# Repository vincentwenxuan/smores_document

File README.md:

# smores_document
smores document for adding comments and documentation to smores program

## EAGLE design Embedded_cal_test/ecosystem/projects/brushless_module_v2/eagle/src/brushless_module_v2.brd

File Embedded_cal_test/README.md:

Embedded
========
Embedded Software for SMORES, including STM32F303 part, ATmega88 part and Gumstix part.

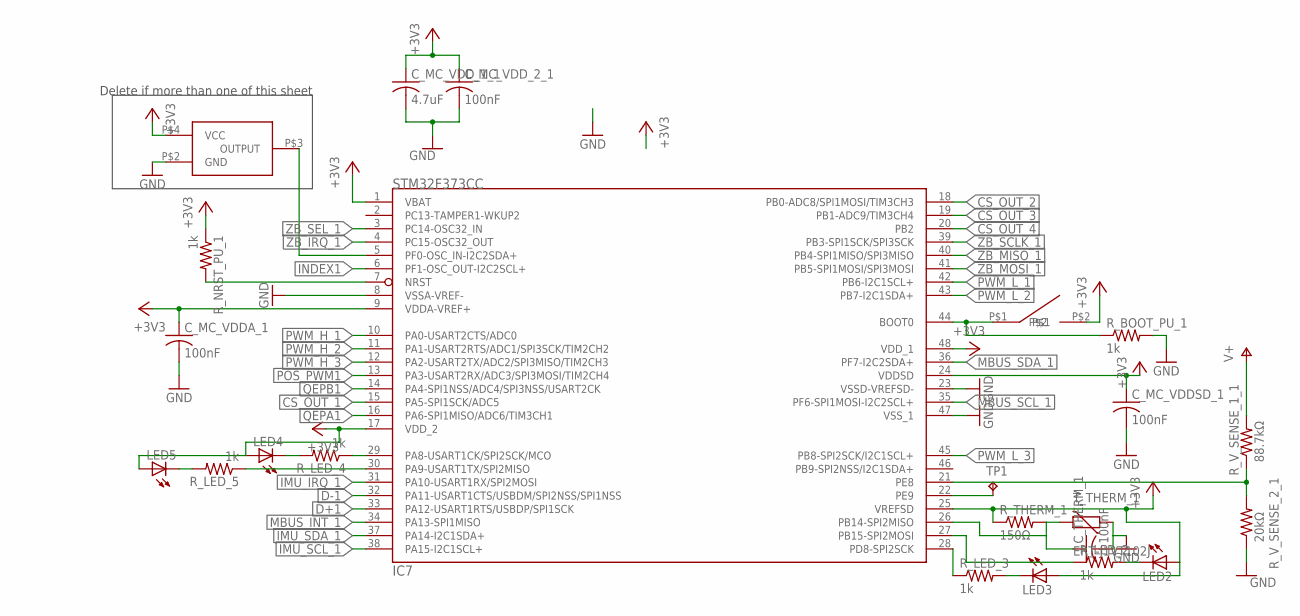
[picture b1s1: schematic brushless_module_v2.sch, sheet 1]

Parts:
C_MC_VDDA_1: 100nF; C0603
C_MC_VDDSD_1: 100nF; C0603
C_MC_VDD_1_1: 4.7uF; C0603
C_MC_VDD_2_1: 100nF; C0603
C_THERM_1: 100nF; C0603
IC7: STM32F373CC; LQFP48
LED2, LED3, LED4, LED5: LEDCHIPLED_0603; CHIPLED_0603
OSC1: FOX924B; 4-SMD_5X3.2
R_BOOT_PU_1: 1k; R0603
R_LED_2, R_LED_3, R_LED_4, R_LED_5: 1k; R0603
R_NRST_PU_1: 1k; R0603
R_THERM_1: 150Ω; R0603
R_V_SENSE_1_1: 88.7kΩ; R0603
R_V_SENSE_2_1: 20kΩ; R0603
SW1: B3U
TP1: TPTP10R; TP10R
T_THERM_1: ERT-J1VT102J; CT/CN0603

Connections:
16MHZ_3V3: IC7.5 (PF0-OSC_IN-I2C2SDA+), OSC1.P$3 (OUTPUT); also elsewhere on the board
+3V3: C_MC_VDDA_1.1, C_MC_VDDSD_1.1, C_MC_VDD_1_1.1, C_MC_VDD_2_1.1, IC7.1 (VBAT), IC7.9 (VDDA-VREF+), IC7.17 (VDD_2), IC7.24 (VDDSD), IC7.25 (VREFSD), IC7.48 (VDD_1), LED2.A, LED3.A, LED4.A, LED5.A, OSC1.P$4 (VCC), R_NRST_PU_1.1, R_THERM_1.1, SW1.P$2; also elsewhere on the board
BOOT0_1: IC7.44 (BOOT0), R_BOOT_PU_1.1, SW1.P$1
CS_OUT_1: IC7.15 (PA5-SPI1SCK/ADC5); also elsewhere on the board
CS_OUT_2: IC7.18 (PB0-ADC8/SPI1MOSI/TIM3CH3); also elsewhere on the board
CS_OUT_3: IC7.19 (PB1-ADC9/TIM3CH4); also elsewhere on the board
CS_OUT_4: IC7.20 (PB2); also elsewhere on the board
D+1: IC7.33 (PA12-USART1RTS/USBDP/SPI1SCK); also elsewhere on the board
D-1: IC7.32 (PA11-USART1CTS/USBDM/SPI2NSS/SPI1NSS); also elsewhere on the board
GND: C_MC_VDDA_1.2, C_MC_VDDSD_1.2, C_MC_VDD_1_1.2, C_MC_VDD_2_1.2, C_THERM_1.2, IC7.8 (VSSA-VREF-), IC7.23 (VSSD-VREFSD-), IC7.47 (VSS_1), OSC1.P$2 (GND), R_BOOT_PU_1.2, R_V_SENSE_2_1.1, T_THERM_1.1; also elsewhere on the board
IMU_IRQ_1: IC7.31 (PA10-USART1RX/SPI2MOSI); also elsewhere on the board
IMU_SCL_1: IC7.38 (PA15-I2C1SCL+); also elsewhere on the board
IMU_SDA_1: IC7.37 (PA14-I2C1SDA+); also elsewhere on the board
INDEX1: IC7.6 (PF1-OSC_OUT-I2C2SCL+); also elsewhere on the board
MBUS_INT_1: IC7.34 (PA13-SPI1MISO); also elsewhere on the board
MBUS_SCL_1: IC7.35 (PF6-SPI1MOSI-I2C2SCL+); also elsewhere on the board
MBUS_SDA_1: IC7.36 (PF7-I2C2SDA+); also elsewhere on the board
unnamed: IC7.21 (PE8), R_V_SENSE_1_1.1, R_V_SENSE_2_1.2
unnamed: LED2.C, R_LED_2.2
unnamed: LED3.C, R_LED_3.2
unnamed: IC7.27 (PB15-SPI2MOSI), R_LED_2.1
unnamed: IC7.28 (PD8-SPI2SCK), R_LED_3.1
unnamed: LED4.C, R_LED_4.2
unnamed: LED5.C, R_LED_5.2
unnamed: IC7.29 (PA8-USART1CK/SPI2SCK/MCO), R_LED_4.1
unnamed: IC7.30 (PA9-USART1TX/SPI2MISO), R_LED_5.1
unnamed: IC7.22 (PE9), TP1.TP
NRST_1: IC7.7 (NRST), R_NRST_PU_1.2
POS_PWM1: IC7.13 (PA3-USART2RX/ADC3/SPI3MOSI/TIM2CH4); also elsewhere on the board
PWM_H_1: IC7.10 (PA0-USART2CTS/ADC0); also elsewhere on the board
PWM_H_2: IC7.11 (PA1-USART2RTS/ADC1/SPI3SCK/TIM2CH2); also elsewhere on the board
PWM_H_3: IC7.12 (PA2-USART2TX/ADC2/SPI3MISO/TIM2CH3); also elsewhere on the board
PWM_L_1: IC7.42 (PB6-I2C1SCL+); also elsewhere on the board
PWM_L_2: IC7.43 (PB7-I2C1SDA+); also elsewhere on the board
PWM_L_3: IC7.45 (PB8-SPI2SCK/I2C1SCL+); also elsewhere on the board
QEPA1: IC7.16 (PA6-SPI1MISO/ADC6/TIM3CH1); also elsewhere on the board
QEPB1: IC7.14 (PA4-SPI1NSS/ADC4/SPI3NSS/USART2CK); also elsewhere on the board
THERM: C_THERM_1.1, IC7.26 (PB14-SPI2MISO), R_THERM_1.2, T_THERM_1.2
V+: R_V_SENSE_1_1.2; also elsewhere on the board
ZB_IRQ_1: IC7.4 (PC15-OSC32_OUT); also elsewhere on the board
ZB_MISO_1: IC7.40 (PB4-SPI1MISO/SPI3MISO); also elsewhere on the board
ZB_MOSI_1: IC7.41 (PB5-SPI1MOSI/SPI3MOSI); also elsewhere on the board
ZB_SCLK_1: IC7.39 (PB3-SPI1SCK/SPI3SCK); also elsewhere on the board
ZB_SEL_1: IC7.3 (PC14-OSC32_IN); also elsewhere on the board

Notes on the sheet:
Delete if more than one of this sheet

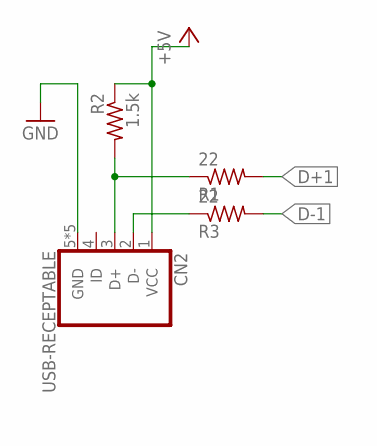
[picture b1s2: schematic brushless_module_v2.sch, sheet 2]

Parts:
CN2: USB-RECEPTABLE; FCI-10103594-0001LF
R1, R3: 22; R0603
R2: 1.5k; R0603

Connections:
+5V: CN2.1 (VCC), R2.1; also elsewhere on the board
D+1: R1.2; also elsewhere on the board
D+_IN_1: CN2.3 (D+), R1.1, R2.2
D-1: R3.2; also elsewhere on the board
D-_IN_1: CN2.2 (D-), R3.1
GND: CN2.5 (GND), CN2.P$1 (GND), CN2.P$2 (GND), CN2.P$3 (GND), CN2.P$4 (GND); also elsewhere on the board

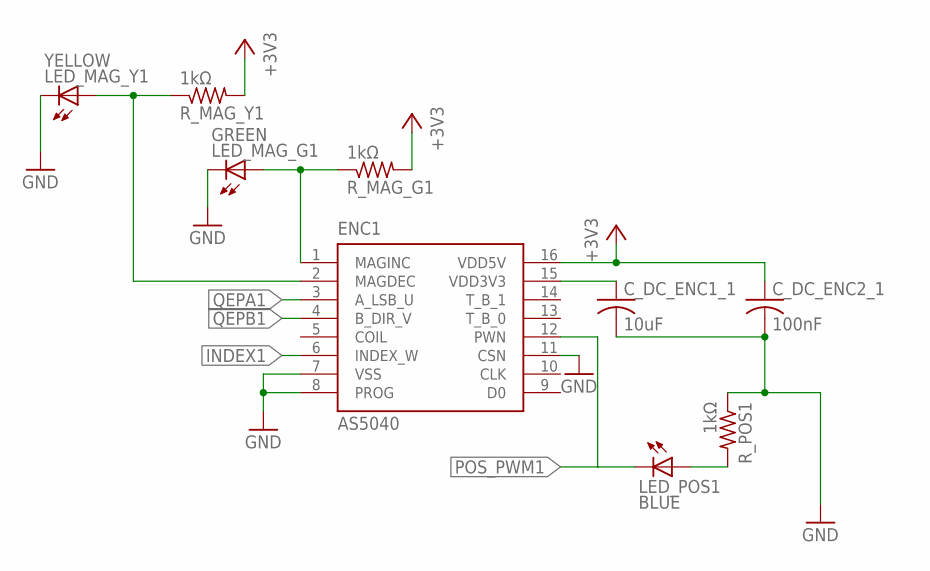
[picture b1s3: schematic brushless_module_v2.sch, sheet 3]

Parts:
C_DC_ENC1_1: 10uF; C0603
C_DC_ENC2_1: 100nF; C0603
ENC1: AS5040; SSOP16
LED_MAG_G1: GREEN; CHIP-LED0603
LED_MAG_Y1: YELLOW; CHIP-LED0603
LED_POS1: BLUE; CHIP-LED0603
R_MAG_G1: 1kΩ; R0603
R_MAG_Y1: 1kΩ; R0603
R_POS1: 1kΩ; R0603

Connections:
+3V3: C_DC_ENC2_1.1, ENC1.16 (VDD5V), R_MAG_G1.2, R_MAG_Y1.2; also elsewhere on the board
ENC_3V3_1: C_DC_ENC1_1.1, ENC1.15 (VDD3V3)
GND: C_DC_ENC1_1.2, C_DC_ENC2_1.2, ENC1.7 (VSS), ENC1.8 (PROG), ENC1.11 (CSN), LED_MAG_G1.C, LED_MAG_Y1.C, R_POS1.1; also elsewhere on the board
INDEX1: ENC1.6 (INDEX_W); also elsewhere on the board
MAGDEC1: ENC1.2 (MAGDEC), LED_MAG_Y1.A, R_MAG_Y1.1
MAGINC1: ENC1.1 (MAGINC), LED_MAG_G1.A, R_MAG_G1.1
unnamed: LED_POS1.A, R_POS1.2
POS_PWM1: ENC1.12 (PWN), LED_POS1.C; also elsewhere on the board
QEPA1: ENC1.3 (A_LSB_U); also elsewhere on the board
QEPB1: ENC1.4 (B_DIR_V); also elsewhere on the board

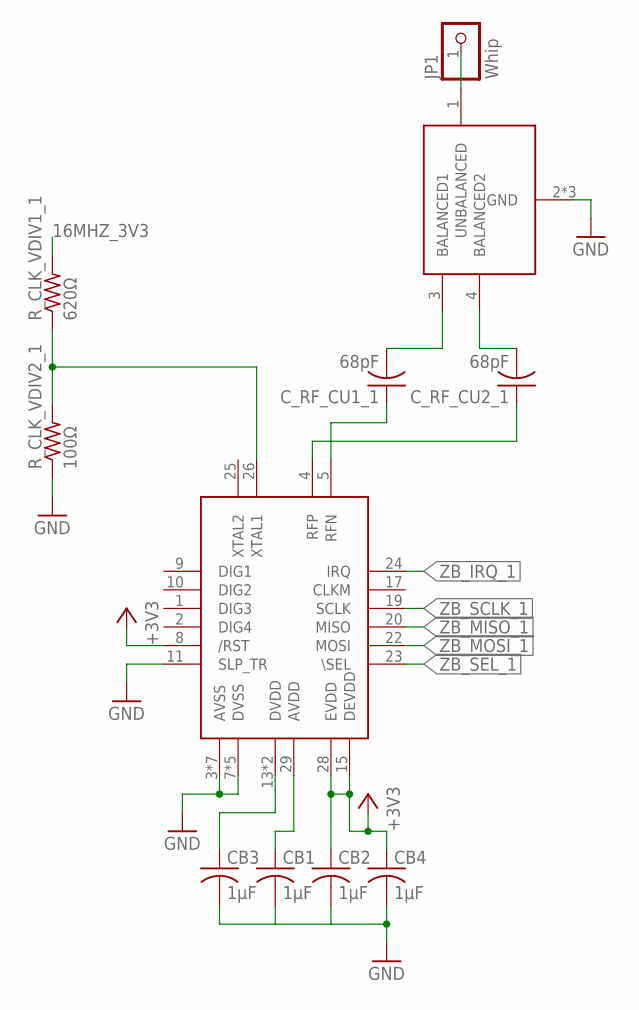
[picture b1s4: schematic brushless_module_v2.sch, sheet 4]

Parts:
BALUN1: 0896FB15A0100
CB1, CB2, CB3, CB4: 1µF; C0603
C_RF_CU1_1, C_RF_CU2_1: 68pF; C0603
JP1: Whip; 1X01M
RADIO1: AT86RF; QFNN32
R_CLK_VDIV1_1: 620Ω; R0603
R_CLK_VDIV2_1: 100Ω; R0603

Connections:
16MHZ_0V5_1: RADIO1.26 (XTAL1), R_CLK_VDIV1_1.1, R_CLK_VDIV2_1.2
16MHZ_3V3: R_CLK_VDIV1_1.2; also elsewhere on the board
+3V3: CB2.1, CB4.1, RADIO1.8 (/RST), RADIO1.15 (DEVDD), RADIO1.28 (EVDD); also elsewhere on the board
ANT1: BALUN1.1 (UNBALANCED), JP1.1
GND: BALUN1.2 (GND), BALUN1.5 (GND), BALUN1.6 (GND), CB1.2, CB2.2, CB3.2, CB4.2, RADIO1.3 (AVSS), RADIO1.6 (AVSS), RADIO1.7 (DVSS), RADIO1.11 (SLP_TR), RADIO1.12 (DVSS), RADIO1.16 (DVSS), RADIO1.18 (DVSS), RADIO1.21 (DVSS), RADIO1.27 (AVSS), RADIO1.30 (AVSS), RADIO1.31 (AVSS), RADIO1.32 (AVSS), RADIO1.EXP (AVSS), R_CLK_VDIV2_1.1; also elsewhere on the board
ZB_AVDD1: CB1.1, RADIO1.29 (AVDD)
ZB_BAL1_1: BALUN1.3 (BALANCED1), C_RF_CU1_1.2
ZB_BAL2_1: BALUN1.4 (BALANCED2), C_RF_CU2_1.2
ZB_DVDD1: CB3.1, RADIO1.13 (DVDD), RADIO1.14 (DVDD)
ZB_IRQ_1: RADIO1.24 (IRQ); also elsewhere on the board
ZB_MISO_1: RADIO1.20 (MISO); also elsewhere on the board
ZB_MOSI_1: RADIO1.22 (MOSI); also elsewhere on the board
ZB_RFN1: C_RF_CU2_1.1, RADIO1.4 (RFP)
ZB_RFP1: C_RF_CU1_1.1, RADIO1.5 (RFN)
ZB_SCLK_1: RADIO1.19 (SCLK); also elsewhere on the board
ZB_SEL_1: RADIO1.23 (\SEL); also elsewhere on the board

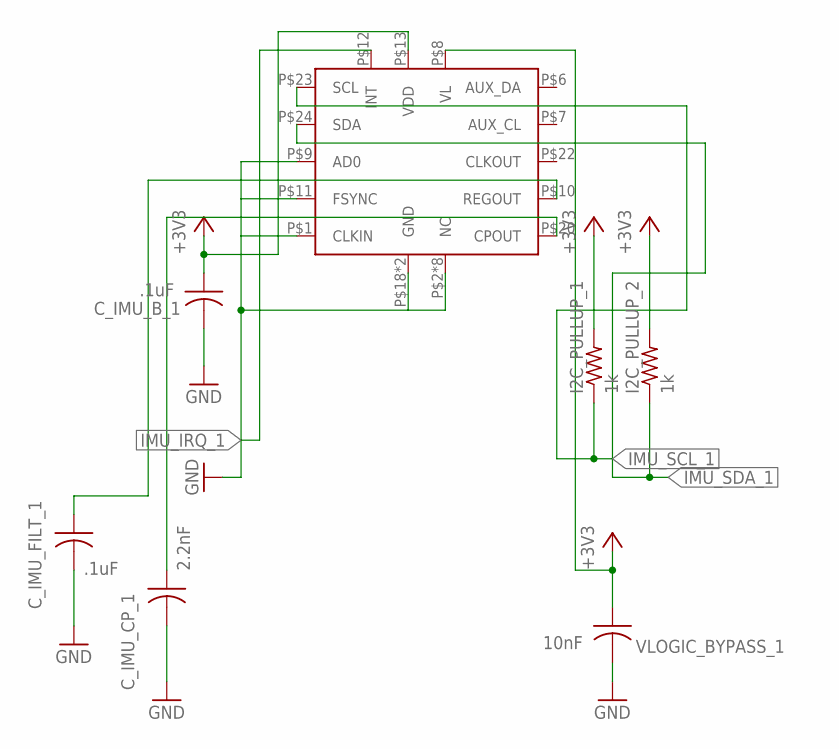
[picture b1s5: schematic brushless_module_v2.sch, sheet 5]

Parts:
C_IMU_B_1: .1uF; C0603
C_IMU_CP_1: 2.2nF; C0603
C_IMU_FILT_1: .1uF; C0603
I2C_PULLUP_1, I2C_PULLUP_2: 1k; R0603
U$10: MPU-6050; QFN24
VLOGIC_BYPASS_1: 10nF; C0603

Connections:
+3V3: C_IMU_B_1.1, I2C_PULLUP_1.2, I2C_PULLUP_2.2, U$10.P$8 (VL), U$10.P$13 (VDD), VLOGIC_BYPASS_1.1; also elsewhere on the board
CPOUT_1: C_IMU_CP_1.1, U$10.P$20 (CPOUT)
GND: C_IMU_B_1.2, C_IMU_CP_1.2, C_IMU_FILT_1.2, U$10.P$1 (CLKIN), U$10.P$2 (NC), U$10.P$3 (NC), U$10.P$4 (NC), U$10.P$5 (NC), U$10.P$9 (AD0), U$10.P$11 (FSYNC), U$10.P$14 (NC), U$10.P$15 (NC), U$10.P$16 (NC), U$10.P$17 (NC), U$10.P$18 (GND), U$10.P$25 (GND), VLOGIC_BYPASS_1.2; also elsewhere on the board
IMU_IRQ_1: U$10.P$12 (INT); also elsewhere on the board
IMU_SCL_1: I2C_PULLUP_1.1, U$10.P$23 (SCL); also elsewhere on the board
IMU_SDA_1: I2C_PULLUP_2.1, U$10.P$24 (SDA); also elsewhere on the board
REGOUT_1: C_IMU_FILT_1.1, U$10.P$10 (REGOUT)

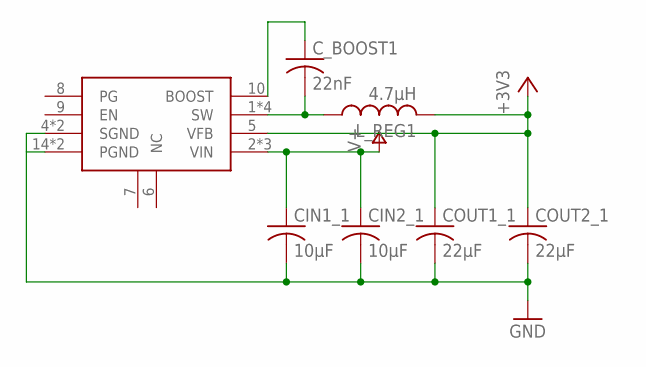
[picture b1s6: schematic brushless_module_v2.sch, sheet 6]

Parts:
CIN1_1, CIN2_1: 10µF; C0805
COUT1_1, COUT2_1: 22µF; C0603
C_BOOST1: 22nF; C0603
L_REG1: 4.7µH; VLC5045
SW_REG1: MCP16323; QFN16

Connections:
+3V3: COUT1_1.1, COUT2_1.1, L_REG1.2, SW_REG1.5 (VFB); also elsewhere on the board
BOOST1: C_BOOST1.1, SW_REG1.10 (BOOST)
GND: CIN1_1.2, CIN2_1.2, COUT1_1.2, COUT2_1.2, SW_REG1.4 (SGND), SW_REG1.14 (PGND), SW_REG1.15 (PGND), SW_REG1.TH (SGND); also elsewhere on the board
SW1: C_BOOST1.2, L_REG1.1, SW_REG1.1 (SW), SW_REG1.12 (SW), SW_REG1.13 (SW), SW_REG1.16 (SW)
V+: CIN1_1.1, CIN2_1.1, SW_REG1.2 (VIN), SW_REG1.3 (VIN), SW_REG1.11 (VIN); also elsewhere on the board

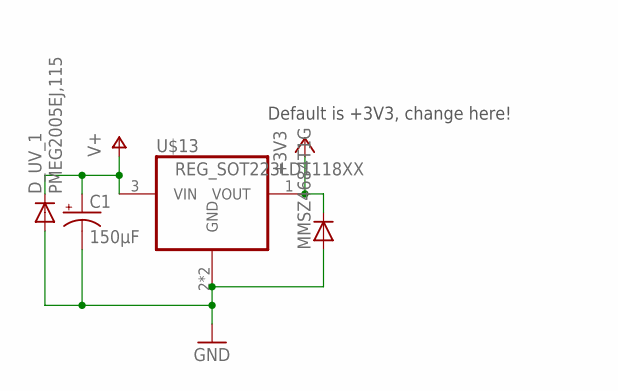
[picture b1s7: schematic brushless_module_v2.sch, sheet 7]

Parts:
C1: 150µF; D/7343-31R
D_UV_1: PMEG2005EJ,115; SOD323-W
MMSZ4684T1G: D-SOD123; SOD123
U$13: REG_SOT223LD1118XX; SOT-223

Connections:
+3V3: MMSZ4684T1G.1 (C), U$13.1 (VOUT); also elsewhere on the board
GND: C1.-, D_UV_1.A, MMSZ4684T1G.2 (A), U$13.2 (GND), U$13.4 (GND); also elsewhere on the board
V+: C1.+, D_UV_1.C, U$13.3 (VIN); also elsewhere on the board

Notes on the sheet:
Default is +3V3, change here!

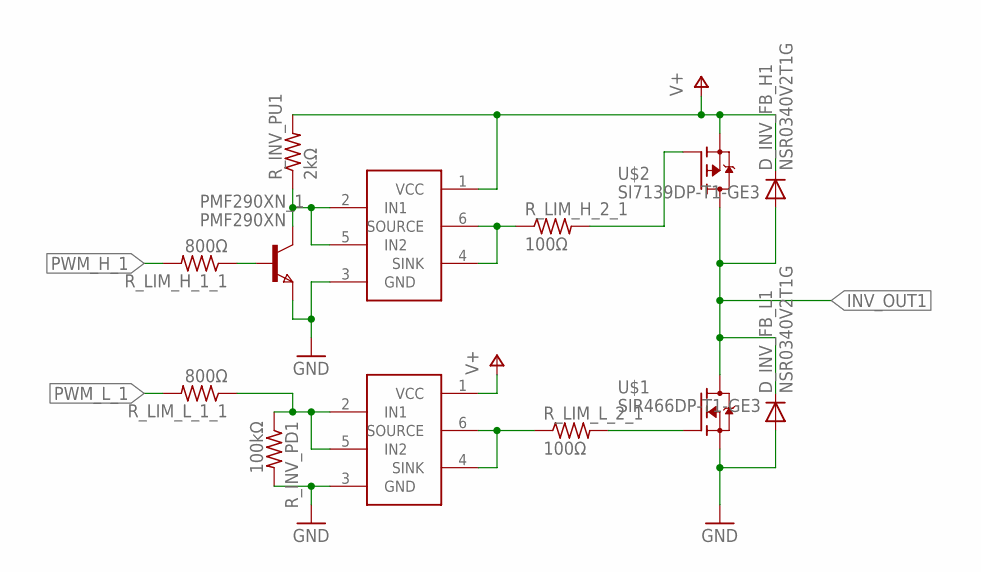
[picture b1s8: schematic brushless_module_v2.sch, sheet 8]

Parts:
D_INV_FB_H1: NSR0340V2T1G; SOD523
D_INV_FB_L1: NSR0340V2T1G; SOD523
PMF290XN_1: PMF290XN; SOT323
R_INV_PD1: 100kΩ; R0603; PART# RNCP0603FTD825RCT-ND
R_INV_PU1: 2kΩ; R0603
R_LIM_H_1_1: 800Ω; R0603
R_LIM_H_2_1: 100Ω; R0603
R_LIM_L_1_1: 800Ω; R0603
R_LIM_L_2_1: 100Ω; R0603
U$1: SIR466DP-T1-GE3; S0-8-POWERPAK
U$2: SI7139DP-T1-GE3; S0-8-POWERPAK
ZXGD3004E6_H_1, ZXGD3004E6_L_1: ZXGD3004E6; SOT23-6

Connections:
GATE_DRV_HIGH_IN1: PMF290XN_1.1 (C), R_INV_PU1.1, ZXGD3004E6_H_1.2 (IN1), ZXGD3004E6_H_1.5 (IN2)
GATE_DRV_LOW_IN1: R_INV_PD1.1, R_LIM_L_1_1.1, ZXGD3004E6_L_1.2 (IN1), ZXGD3004E6_L_1.5 (IN2)
GND: D_INV_FB_L1.A, PMF290XN_1.3 (E), R_INV_PD1.2, U$1.1 (S), U$1.2 (S), U$1.3 (S), ZXGD3004E6_H_1.3 (GND), ZXGD3004E6_L_1.3 (GND); also elsewhere on the board
INV_HIGH_GATE1: R_LIM_H_2_1.2, U$2.4 (G)
INV_HIGH_GSS1: R_LIM_H_2_1.1, ZXGD3004E6_H_1.4 (SINK), ZXGD3004E6_H_1.6 (SOURCE)
INV_LOW_GATE1: R_LIM_L_2_1.2, U$1.4 (G)
INV_LOW_GSS1: R_LIM_L_2_1.1, ZXGD3004E6_L_1.4 (SINK), ZXGD3004E6_L_1.6 (SOURCE)
INV_OUT1: D_INV_FB_H1.A, D_INV_FB_L1.C, U$1.5 (D), U$1.6 (D), U$1.7 (D), U$1.8 (D), U$1.P$1 (D), U$2.5 (D), U$2.6 (D), U$2.7 (D), U$2.8 (D), U$2.P$1 (D); also elsewhere on the board
unnamed: PMF290XN_1.2 (B), R_LIM_H_1_1.1
PWM_H_1: R_LIM_H_1_1.2; also elsewhere on the board
PWM_L_1: R_LIM_L_1_1.2; also elsewhere on the board
V+: D_INV_FB_H1.C, R_INV_PU1.2, U$2.1 (S), U$2.2 (S), U$2.3 (S), ZXGD3004E6_H_1.1 (VCC), ZXGD3004E6_L_1.1 (VCC); also elsewhere on the board

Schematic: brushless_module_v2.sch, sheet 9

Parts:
D_INV_FB_H2: NSR0340V2T1G; SOD523
D_INV_FB_L2: NSR0340V2T1G; SOD523
PMF290XN_2: PMF290XN; SOT323
R_INV_PD2: 100kΩ; R0603; PART# RNCP0603FTD825RCT-ND
R_INV_PU2: 2kΩ; R0603
R_LIM_H_1_2: 800Ω; R0603
R_LIM_H_2_2: 100Ω; R0603
R_LIM_L_1_2: 800Ω; R0603
R_LIM_L_2_2: 100Ω; R0603
U$3: SIR466DP-T1-GE3; S0-8-POWERPAK
U$4: SI7139DP-T1-GE3; S0-8-POWERPAK
ZXGD3004E6_H_2, ZXGD3004E6_L_2: ZXGD3004E6; SOT23-6

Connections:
GATE_DRV_HIGH_IN2: PMF290XN_2.1 (C), R_INV_PU2.1, ZXGD3004E6_H_2.2 (IN1), ZXGD3004E6_H_2.5 (IN2)
GATE_DRV_LOW_IN2: R_INV_PD2.1, R_LIM_L_1_2.1, ZXGD3004E6_L_2.2 (IN1), ZXGD3004E6_L_2.5 (IN2)
GND: D_INV_FB_L2.A, PMF290XN_2.3 (E), R_INV_PD2.2, U$3.1 (S), U$3.2 (S), U$3.3 (S), ZXGD3004E6_H_2.3 (GND), ZXGD3004E6_L_2.3 (GND); also elsewhere on the board
INV_HIGH_GATE2: R_LIM_H_2_2.2, U$4.4 (G)
INV_HIGH_GSS2: R_LIM_H_2_2.1, ZXGD3004E6_H_2.4 (SINK), ZXGD3004E6_H_2.6 (SOURCE)
INV_LOW_GATE2: R_LIM_L_2_2.2, U$3.4 (G)
INV_LOW_GSS2: R_LIM_L_2_2.1, ZXGD3004E6_L_2.4 (SINK), ZXGD3004E6_L_2.6 (SOURCE)
INV_OUT2: D_INV_FB_H2.A, D_INV_FB_L2.C, U$3.5 (D), U$3.6 (D), U$3.7 (D), U$3.8 (D), U$3.P$1 (D), U$4.5 (D), U$4.6 (D), U$4.7 (D), U$4.8 (D), U$4.P$1 (D); also elsewhere on the board
unnamed: PMF290XN_2.2 (B), R_LIM_H_1_2.1
PWM_H_2: R_LIM_H_1_2.2; also elsewhere on the board
PWM_L_2: R_LIM_L_1_2.2; also elsewhere on the board
V+: D_INV_FB_H2.C, R_INV_PU2.2, U$4.1 (S), U$4.2 (S), U$4.3 (S), ZXGD3004E6_H_2.1 (VCC), ZXGD3004E6_L_2.1 (VCC); also elsewhere on the board

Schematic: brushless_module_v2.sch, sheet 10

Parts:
D_INV_FB_H3: NSR0340V2T1G; SOD523
D_INV_FB_L3: NSR0340V2T1G; SOD523
PMF290XN_3: PMF290XN; SOT323
R_INV_PD3: 100kΩ; R0603; PART# RNCP0603FTD825RCT-ND
R_INV_PU3: 2kΩ; R0603
R_LIM_H_1_3: 800Ω; R0603
R_LIM_H_2_3: 100Ω; R0603
R_LIM_L_1_3: 800Ω; R0603
R_LIM_L_2_3: 100Ω; R0603
U$5: SIR466DP-T1-GE3; S0-8-POWERPAK
U$6: SI7139DP-T1-GE3; S0-8-POWERPAK
ZXGD3004E6_H_3, ZXGD3004E6_L_3: ZXGD3004E6; SOT23-6

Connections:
GATE_DRV_HIGH_IN3: PMF290XN_3.1 (C), R_INV_PU3.1, ZXGD3004E6_H_3.2 (IN1), ZXGD3004E6_H_3.5 (IN2)
GATE_DRV_LOW_IN3: R_INV_PD3.1, R_LIM_L_1_3.1, ZXGD3004E6_L_3.2 (IN1), ZXGD3004E6_L_3.5 (IN2)
GND: D_INV_FB_L3.A, PMF290XN_3.3 (E), R_INV_PD3.2, U$5.1 (S), U$5.2 (S), U$5.3 (S), ZXGD3004E6_H_3.3 (GND), ZXGD3004E6_L_3.3 (GND); also elsewhere on the board
INV_HIGH_GATE3: R_LIM_H_2_3.2, U$6.4 (G)
INV_HIGH_GSS3: R_LIM_H_2_3.1, ZXGD3004E6_H_3.4 (SINK), ZXGD3004E6_H_3.6 (SOURCE)
INV_LOW_GATE3: R_LIM_L_2_3.2, U$5.4 (G)
INV_LOW_GSS3: R_LIM_L_2_3.1, ZXGD3004E6_L_3.4 (SINK), ZXGD3004E6_L_3.6 (SOURCE)
INV_OUT3: D_INV_FB_H3.A, D_INV_FB_L3.C, U$5.5 (D), U$5.6 (D), U$5.7 (D), U$5.8 (D), U$5.P$1 (D), U$6.5 (D), U$6.6 (D), U$6.7 (D), U$6.8 (D), U$6.P$1 (D); also elsewhere on the board
unnamed: PMF290XN_3.2 (B), R_LIM_H_1_3.1
PWM_H_3: R_LIM_H_1_3.2; also elsewhere on the board
PWM_L_3: R_LIM_L_1_3.2; also elsewhere on the board
V+: D_INV_FB_H3.C, R_INV_PU3.2, U$6.1 (S), U$6.2 (S), U$6.3 (S), ZXGD3004E6_H_3.1 (VCC), ZXGD3004E6_L_3.1 (VCC); also elsewhere on the board

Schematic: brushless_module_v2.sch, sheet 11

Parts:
CS_1: INA21X; SC70
C_CS_DC_1: 100nF; C0603
R_CS_1: 1mΩ; R1206

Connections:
CS_OUT_1: CS_1.P6 (OUT); also elsewhere on the board
GND: CS_1.P2 (GND), C_CS_DC_1.2; also elsewhere on the board
INV_OUT1: CS_1.P4 (IN+), R_CS_1.2; also elsewhere on the board
MOTOR_1: CS_1.P5 (IN-), R_CS_1.1; also elsewhere on the board
V+: CS_1.P3 (V+), C_CS_DC_1.1; also elsewhere on the board
V_REF_CS: CS_1.P1 (REF); also elsewhere on the board

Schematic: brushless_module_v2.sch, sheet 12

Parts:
CS_2: INA21X; SC70
C_CS_DC_2: 100nF; C0603
R_CS_2: 1mΩ; R1206

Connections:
CS_OUT_2: CS_2.P6 (OUT); also elsewhere on the board
GND: CS_2.P2 (GND), C_CS_DC_2.2; also elsewhere on the board
INV_OUT2: CS_2.P5 (IN-), R_CS_2.2; also elsewhere on the board
MOTOR_2: CS_2.P4 (IN+), R_CS_2.1; also elsewhere on the board
V+: CS_2.P3 (V+), C_CS_DC_2.1; also elsewhere on the board
V_REF_CS: CS_2.P1 (REF); also elsewhere on the board

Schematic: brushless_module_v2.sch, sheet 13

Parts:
CS_3: INA21X; SC70
C_CS_DC_3: 100nF; C0603
R_CS_3: 1mΩ; R1206

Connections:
CS_OUT_3: CS_3.P6 (OUT); also elsewhere on the board
GND: CS_3.P2 (GND), C_CS_DC_3.2; also elsewhere on the board
INV_OUT3: CS_3.P4 (IN+), R_CS_3.2; also elsewhere on the board
MOTOR_3: CS_3.P5 (IN-), R_CS_3.1; also elsewhere on the board
V+: CS_3.P3 (V+), C_CS_DC_3.1; also elsewhere on the board
V_REF_CS: CS_3.P1 (REF); also elsewhere on the board

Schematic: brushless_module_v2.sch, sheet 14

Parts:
CS_4: INA21X; SC70
C_CS_DC_4: 100nF; C0603
C_S_1: 6.47uF; C0603
R_CS_4: 1mΩ; R1206
R_CS_REF1_4, R_CS_REF2_4: 10kΩ; R0603
R_S1_1, R_S2_1: 10Ω; R0603

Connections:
+3V3: R_CS_REF1_4.2; also elsewhere on the board
CS_OUT_4: CS_4.P6 (OUT); also elsewhere on the board
GND: CS_4.P2 (GND), C_CS_DC_4.2, R_CS_REF2_4.1; also elsewhere on the board
IN+_1: CS_4.P4 (IN+), C_S_1.1, R_S2_1.1
IN-_1: CS_4.P5 (IN-), C_S_1.2, R_S1_1.1
V+: R_CS_4.1, R_S1_1.2; also elsewhere on the board
V_BATT: CS_4.P3 (V+), C_CS_DC_4.1, R_CS_4.2, R_S2_1.2; also elsewhere on the board
V_REF_CS: CS_4.P1 (REF), R_CS_REF1_4.1, R_CS_REF2_4.2; also elsewhere on the board

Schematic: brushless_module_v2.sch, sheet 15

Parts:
C2: 0.1uF; C0603
C3: 10uF; C0603
D_OV_1: PMEG2005EJ,115; SOD323-W
FPF2123: FPF2123; SOT23-5L
R4: 1MΩ; R0603
R6: 604Ω; R0603

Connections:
+5V: C3.1, FPF2123.1 (VIN), FPF2123.3 (ON); also elsewhere on the board
GND: C2.2, C3.2, FPF2123.2 (GND), R4.1, R6.1; also elsewhere on the board
LOAD_ISET_1: FPF2123.4 (ISET), R6.2
unnamed: D_OV_1.A, FPF2123.5 (VOUT), R4.2
V+: C2.1, D_OV_1.C; also elsewhere on the board

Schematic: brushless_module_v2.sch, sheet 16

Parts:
R11, R12: 1k; R0603
U$7: SM05B-GHS-TB

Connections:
+3V3: R11.2, R12.2, U$7.P$3 (3); also elsewhere on the board
GND: U$7.P$5 (5); also elsewhere on the board
MBUS_INT_1: U$7.P$1 (1); also elsewhere on the board
MBUS_SCL_1: R12.1, U$7.P$4 (4); also elsewhere on the board
MBUS_SDA_1: R11.1, U$7.P$2 (2); also elsewhere on the board

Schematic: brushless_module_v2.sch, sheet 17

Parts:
U$8: DEANS-MICRO-2PIN
U$9: DEANS-MICRO-3PIN

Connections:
GND: U$8.P$2 (2); also elsewhere on the board
MOTOR_1: U$9.P$1 (1); also elsewhere on the board
MOTOR_2: U$9.P$2 (2); also elsewhere on the board
MOTOR_3: U$9.P$3 (3); also elsewhere on the board
V_BATT: U$8.P$1 (1); also elsewhere on the board

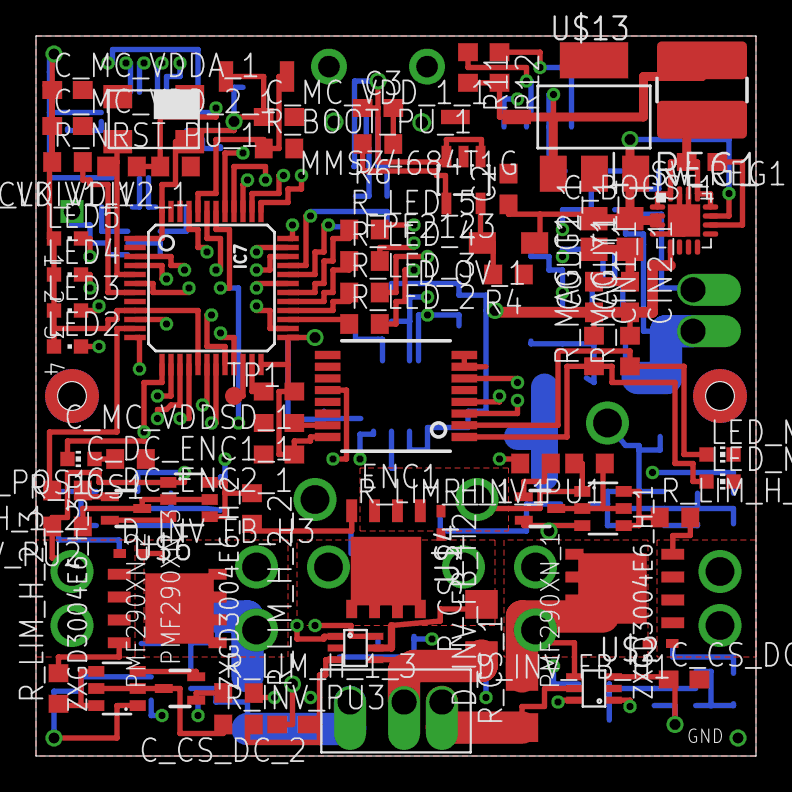
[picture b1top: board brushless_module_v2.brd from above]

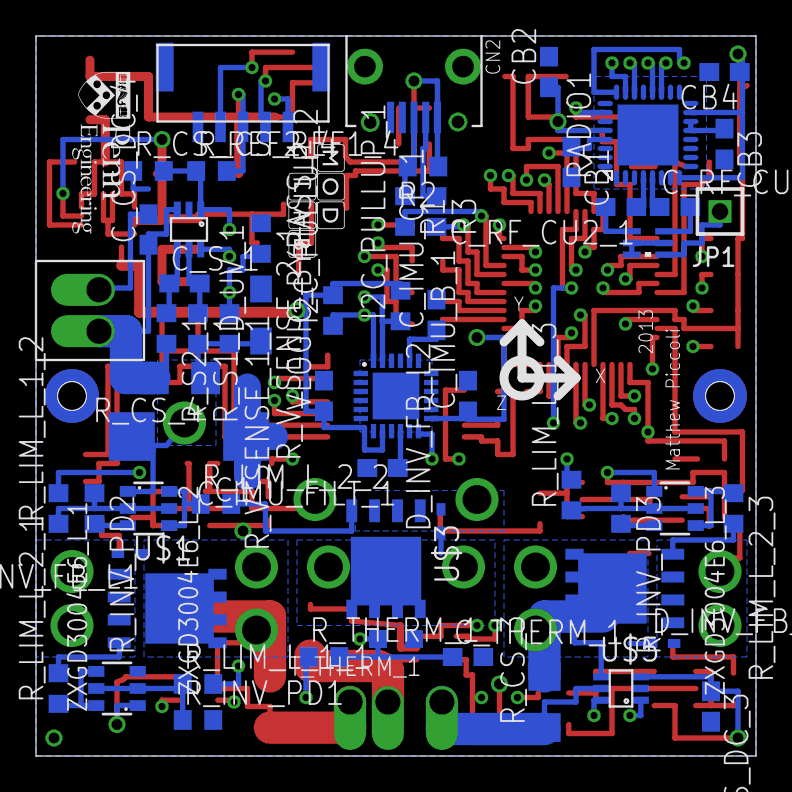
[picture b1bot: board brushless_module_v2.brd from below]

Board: 2 copper layers, 40.0 x 40.0 mm, 134 parts (60 on the bottom side), 96 nets.

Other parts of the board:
U$11: PENN_ENGINEERING
U$12: MODLAB

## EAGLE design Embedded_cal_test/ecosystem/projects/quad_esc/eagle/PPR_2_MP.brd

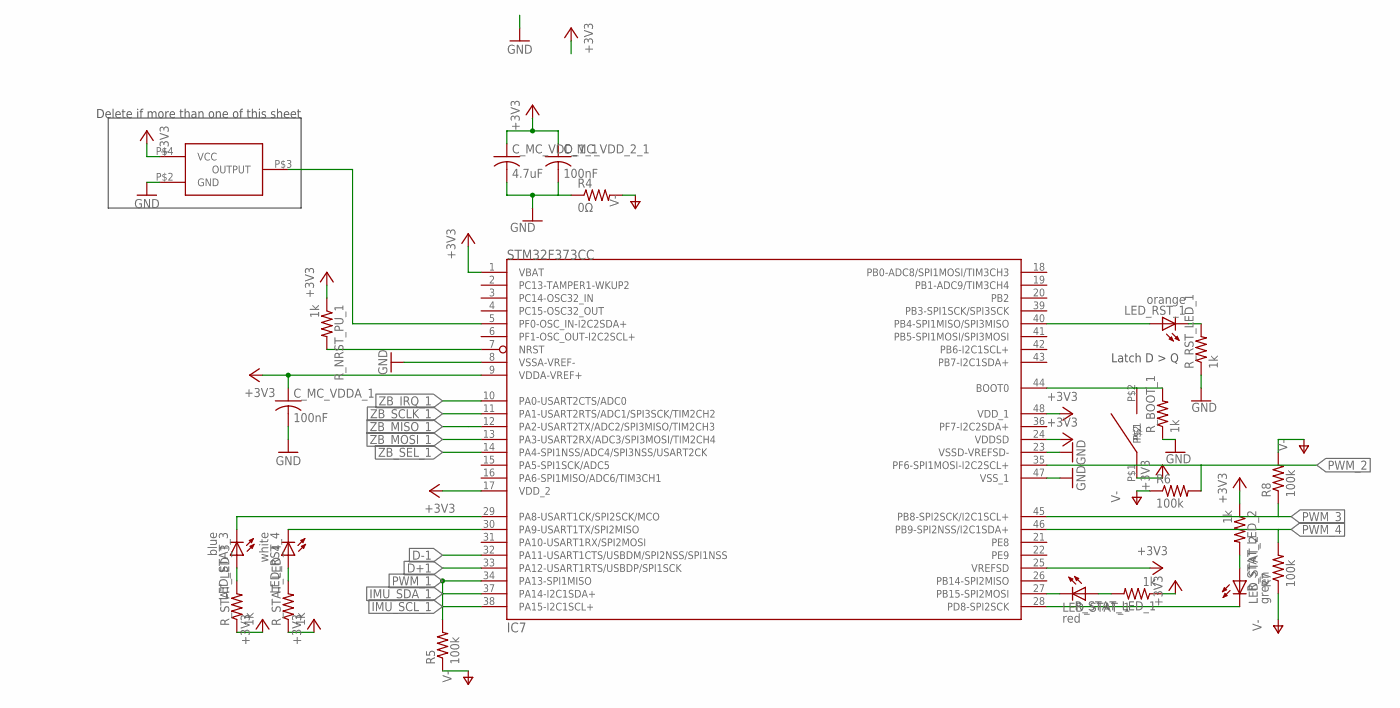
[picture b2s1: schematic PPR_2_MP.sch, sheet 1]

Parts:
C_MC_VDDA_1: 100nF; C0603
C_MC_VDD_1_1: 4.7uF; C0603
C_MC_VDD_2_1: 100nF; C0603
IC7: STM32F373CC; LQFP48
LED_RST_1: orange; CHIPLED_0603
LED_RST_4: white; CHIPLED_0603
LED_STAT_1: red; CHIPLED_0603
LED_STAT_2: green; CHIPLED_0603
LED_STAT_3: blue; CHIPLED_0603
OSC1: FOX924B; 4-SMD_5X3.2
R4: 0Ω; R0603
R5, R6, R7, R8: 100k; R0603
R_BOOT_1: 1k; R0603
R_NRST_PU_1: 1k; R0603
R_RST_LED_1: 1k; R0603
R_STAT_LED_1, R_STAT_LED_2, R_STAT_LED_3, R_STAT_LED_4: 1k; R0603
SW1: B3U

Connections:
16MHZ_3V3: IC7.5 (PF0-OSC_IN-I2C2SDA+), OSC1.P$3 (OUTPUT); also elsewhere on the board
+3V3: C_MC_VDDA_1.1, C_MC_VDD_1_1.1, C_MC_VDD_2_1.1, IC7.1 (VBAT), IC7.9 (VDDA-VREF+), IC7.17 (VDD_2), IC7.24 (VDDSD), IC7.25 (VREFSD), IC7.48 (VDD_1), OSC1.P$4 (VCC), R_NRST_PU_1.1, R_STAT_LED_1.1, R_STAT_LED_2.1, R_STAT_LED_3.1, R_STAT_LED_4.1, SW1.P$1; also elsewhere on the board
BOOT0_1: IC7.44 (BOOT0), R_BOOT_1.2, SW1.P$2
D+1: IC7.33 (PA12-USART1RTS/USBDP/SPI1SCK); also elsewhere on the board
D-1: IC7.32 (PA11-USART1CTS/USBDM/SPI2NSS/SPI1NSS); also elsewhere on the board
GND: C_MC_VDDA_1.2, C_MC_VDD_1_1.2, C_MC_VDD_2_1.2, IC7.8 (VSSA-VREF-), IC7.23 (VSSD-VREFSD-), IC7.47 (VSS_1), OSC1.P$2 (GND), R4.1, R_BOOT_1.1, R_RST_LED_1.1; also elsewhere on the board
IMU_SCL_1: IC7.38 (PA15-I2C1SCL+); also elsewhere on the board
IMU_SDA_1: IC7.37 (PA14-I2C1SDA+); also elsewhere on the board
LED_RST_1_1: IC7.40 (PB4-SPI1MISO/SPI3MISO), LED_RST_1.A
LED_RST_2_1: LED_RST_1.C, R_RST_LED_1.2
unnamed: IC7.27 (PB15-SPI2MOSI), LED_STAT_1.C
unnamed: LED_STAT_1.A, R_STAT_LED_1.2
unnamed: LED_STAT_2.A, R_STAT_LED_2.2
unnamed: IC7.28 (PD8-SPI2SCK), LED_STAT_2.C
unnamed: LED_STAT_3.A, R_STAT_LED_3.2
unnamed: LED_RST_4.A, R_STAT_LED_4.2
unnamed: IC7.30 (PA9-USART1TX/SPI2MISO), LED_RST_4.C
unnamed: IC7.29 (PA8-USART1CK/SPI2SCK/MCO), LED_STAT_3.C
NRST_1: IC7.7 (NRST), R_NRST_PU_1.2
PWM_1: IC7.34 (PA13-SPI1MISO), R5.2; also elsewhere on the board
PWM_2: IC7.35 (PF6-SPI1MOSI-I2C2SCL+), R6.2; also elsewhere on the board
PWM_3: IC7.45 (PB8-SPI2SCK/I2C1SCL+), R8.1; also elsewhere on the board
PWM_4: IC7.46 (PB9-SPI2NSS/I2C1SDA+), R7.2; also elsewhere on the board
V-: R4.2, R5.1, R6.1, R7.1, R8.2; also elsewhere on the board
ZB_IRQ_1: IC7.10 (PA0-USART2CTS/ADC0); also elsewhere on the board
ZB_MISO_1: IC7.12 (PA2-USART2TX/ADC2/SPI3MISO/TIM2CH3); also elsewhere on the board
ZB_MOSI_1: IC7.13 (PA3-USART2RX/ADC3/SPI3MOSI/TIM2CH4); also elsewhere on the board
ZB_SCLK_1: IC7.11 (PA1-USART2RTS/ADC1/SPI3SCK/TIM2CH2); also elsewhere on the board
ZB_SEL_1: IC7.14 (PA4-SPI1NSS/ADC4/SPI3NSS/USART2CK); also elsewhere on the board

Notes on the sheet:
Latch D > Q
Delete if more than one of this sheet

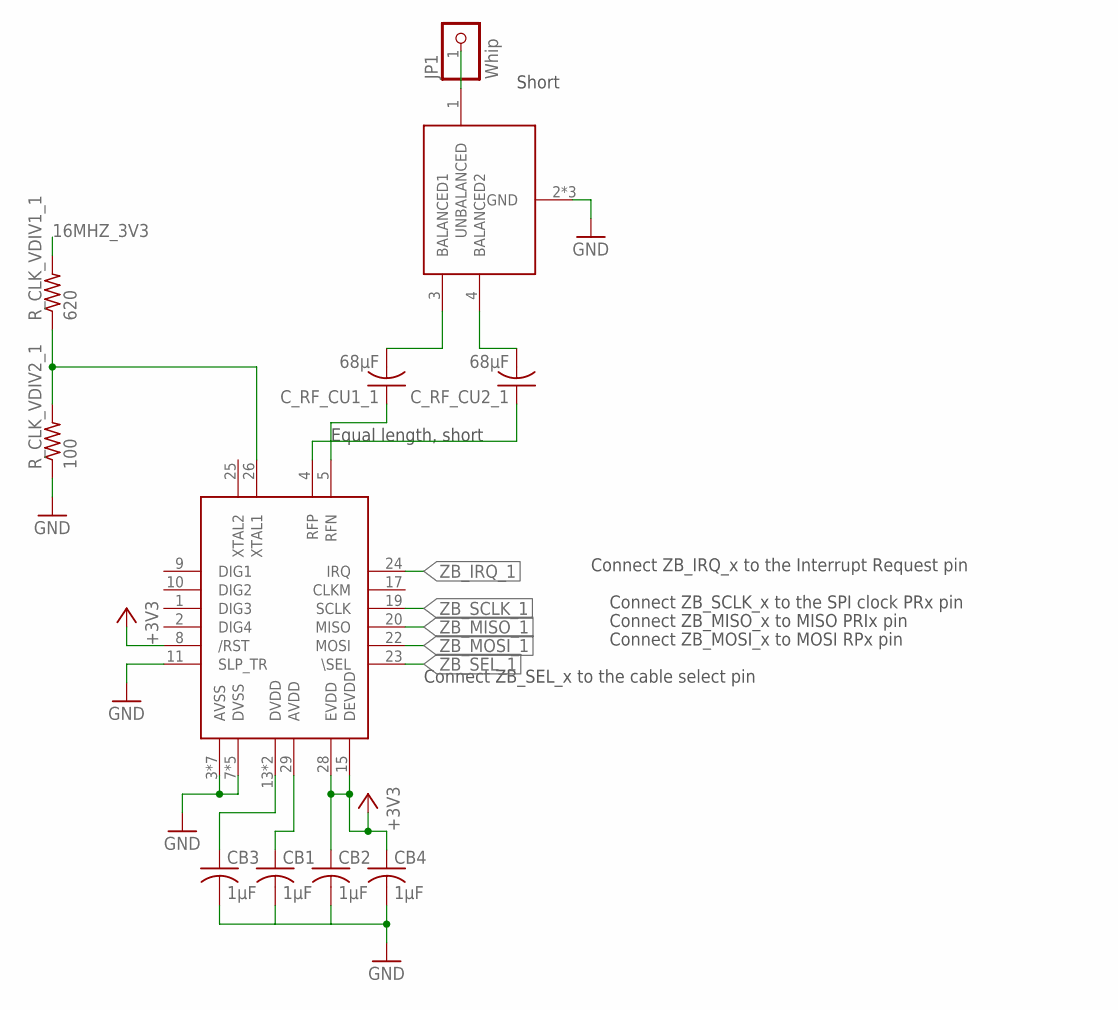
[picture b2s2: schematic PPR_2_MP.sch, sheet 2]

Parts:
BALUN1: 0896FB15A0100
CB1, CB2, CB3, CB4: 1µF; C0603
C_RF_CU1_1, C_RF_CU2_1: 68µF; C0603
JP1: Whip; 1X01M
RADIO1: AT86RF; QFNN32
R_CLK_VDIV1_1: 620; R0603
R_CLK_VDIV2_1: 100; R0603

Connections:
16MHZ_0V5_AC1: RADIO1.26 (XTAL1), R_CLK_VDIV1_1.1, R_CLK_VDIV2_1.2
16MHZ_3V3: R_CLK_VDIV1_1.2; also elsewhere on the board
+3V3: CB2.1, CB4.1, RADIO1.8 (/RST), RADIO1.15 (DEVDD), RADIO1.28 (EVDD); also elsewhere on the board
ANT1: BALUN1.1 (UNBALANCED), JP1.1
GND: BALUN1.2 (GND), BALUN1.5 (GND), BALUN1.6 (GND), CB1.2, CB2.2, CB3.2, CB4.2, RADIO1.3 (AVSS), RADIO1.6 (AVSS), RADIO1.7 (DVSS), RADIO1.11 (SLP_TR), RADIO1.12 (DVSS), RADIO1.16 (DVSS), RADIO1.18 (DVSS), RADIO1.21 (DVSS), RADIO1.27 (AVSS), RADIO1.30 (AVSS), RADIO1.31 (AVSS), RADIO1.32 (AVSS), RADIO1.EXP (AVSS), R_CLK_VDIV2_1.1; also elsewhere on the board
ZB_AVDD1: CB1.1, RADIO1.29 (AVDD)
ZB_BAL1_1: BALUN1.3 (BALANCED1), C_RF_CU1_1.2
ZB_BAL2_1: BALUN1.4 (BALANCED2), C_RF_CU2_1.2
ZB_DVDD1: CB3.1, RADIO1.13 (DVDD), RADIO1.14 (DVDD)
ZB_IRQ_1: RADIO1.24 (IRQ); also elsewhere on the board
ZB_MISO_1: RADIO1.20 (MISO); also elsewhere on the board
ZB_MOSI_1: RADIO1.22 (MOSI); also elsewhere on the board
ZB_RFN1: C_RF_CU2_1.1, RADIO1.4 (RFP)
ZB_RFP1: C_RF_CU1_1.1, RADIO1.5 (RFN)
ZB_SCLK_1: RADIO1.19 (SCLK); also elsewhere on the board
ZB_SEL_1: RADIO1.23 (\SEL); also elsewhere on the board

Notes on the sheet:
Connect ZB_SEL_x to the cable select pin
Connect ZB_MOSI_x to MOSI RPx pin
Connect ZB_SCLK_x to the SPI clock PRx pin
Connect ZB_MISO_x to MISO PRIx pin
Connect ZB_IRQ_x to the Interrupt Request pin
Equal length, short
Short

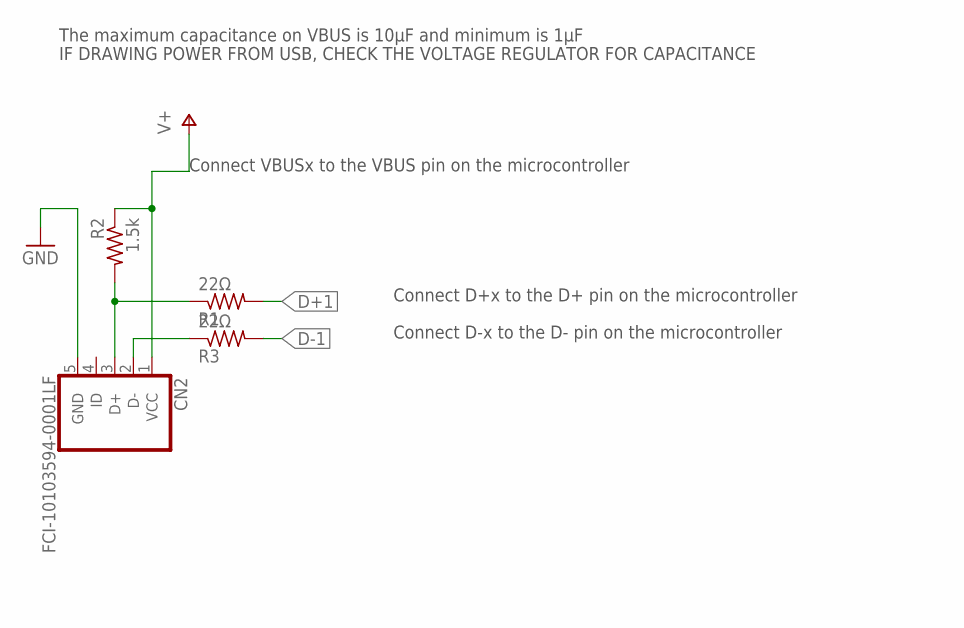
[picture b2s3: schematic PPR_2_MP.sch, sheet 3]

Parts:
CN2: FCI-10103594-0001LF
R1, R3: 22Ω; R0402
R2: 1.5k; R0402

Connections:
D+1: R1.2; also elsewhere on the board
D+_IN_1: CN2.3 (D+), R1.1, R2.2
D-1: R3.2; also elsewhere on the board
D-_IN_1: CN2.2 (D-), R3.1
GND: CN2.5 (GND); also elsewhere on the board
V+: CN2.1 (VCC), R2.1; also elsewhere on the board

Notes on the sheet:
Connect VBUSx to the VBUS pin on the microcontroller
Connect D+x to the D+ pin on the microcontroller
Connect D-x to the D- pin on the microcontroller
The maximum capacitance on VBUS is 10µF and minimum is 1µF
IF DRAWING POWER FROM USB, CHECK THE VOLTAGE REGULATOR FOR CAPACITANCE

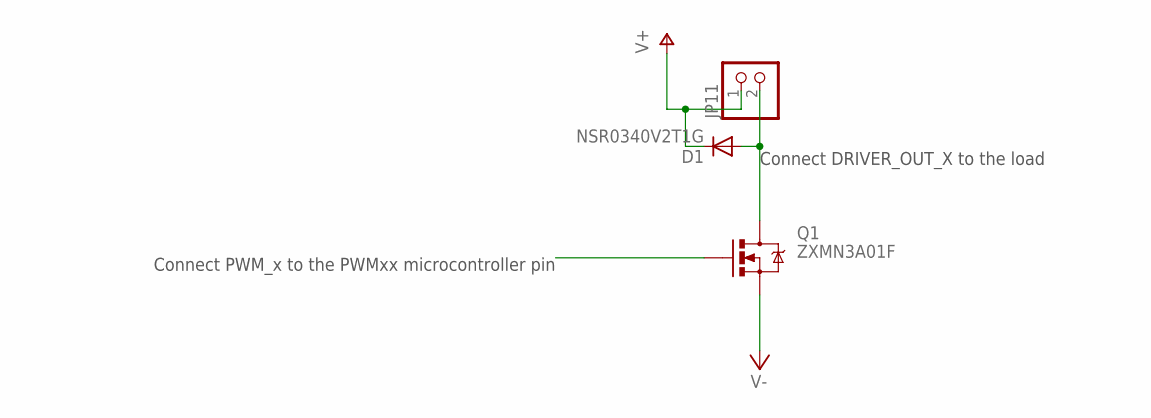
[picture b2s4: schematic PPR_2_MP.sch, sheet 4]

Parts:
D1: NSR0340V2T1G; SOD523
JP11: PINHD-1X2; 1X02
Q1: ZXMN3A01F; SOT23-3

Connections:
DRIVER_OUT_1: D1.A, JP11.2, Q1.3 (D)
PWM_1: Q1.1 (G); also elsewhere on the board
V+: D1.C, JP11.1; also elsewhere on the board
V-: Q1.2 (S); also elsewhere on the board

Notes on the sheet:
Connect PWM_x to the PWMxx microcontroller pin
Connect DRIVER_OUT_X to the load

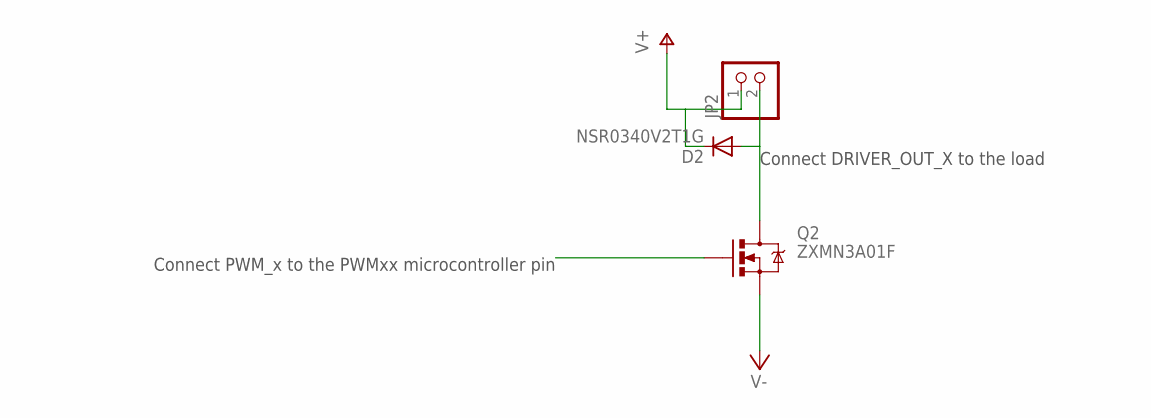
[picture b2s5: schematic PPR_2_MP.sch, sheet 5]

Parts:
D2: NSR0340V2T1G; SOD523
JP2: PINHD-1X2; 1X02
Q2: ZXMN3A01F; SOT23-3

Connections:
DRIVER_OUT_2: D2.A, JP2.2, Q2.3 (D)
PWM_2: Q2.1 (G); also elsewhere on the board
V+: D2.C, JP2.1; also elsewhere on the board
V-: Q2.2 (S); also elsewhere on the board

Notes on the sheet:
Connect PWM_x to the PWMxx microcontroller pin
Connect DRIVER_OUT_X to the load

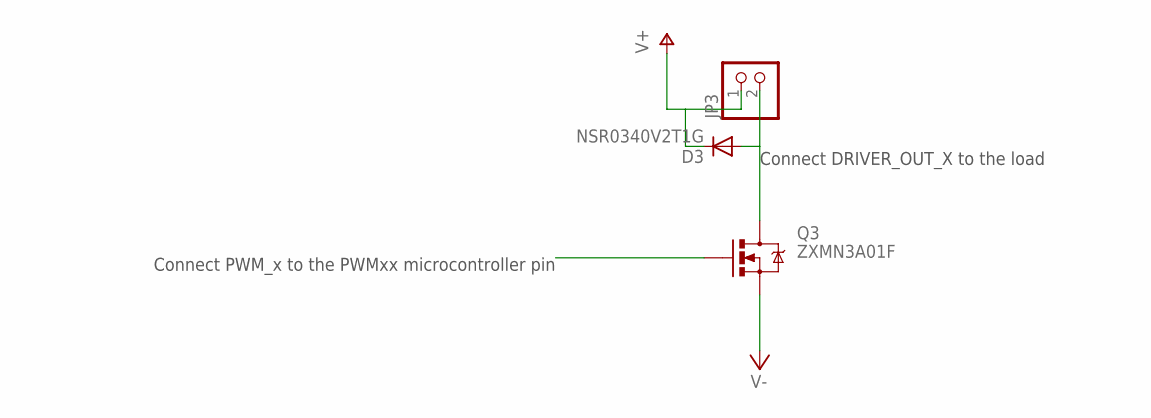
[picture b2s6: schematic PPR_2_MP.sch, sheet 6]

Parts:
D3: NSR0340V2T1G; SOD523
JP3: PINHD-1X2; 1X02
Q3: ZXMN3A01F; SOT23-3

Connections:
DRIVER_OUT_3: D3.A, JP3.2, Q3.3 (D)
PWM_3: Q3.1 (G); also elsewhere on the board
V+: D3.C, JP3.1; also elsewhere on the board
V-: Q3.2 (S); also elsewhere on the board

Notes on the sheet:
Connect PWM_x to the PWMxx microcontroller pin
Connect DRIVER_OUT_X to the load

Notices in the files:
parts and their libraries:
SparkFun: Licensing: CC v3.0 Share-Alike You are welcome to use this library for commercial purposes.
